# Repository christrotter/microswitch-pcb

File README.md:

# microswitch-pcb
Designed for use on the [ArcPedals mk2](https://github.com/christrotter/qmk_firmware/tree/arcboard-series/keyboards/handwired/arcpedals_mk2) - with the accompanying files, a drop-in replacement for the old MX-based switches.

JLC wanted to charge me extra for using SK6812-MINI-E leds, so I swapped over to the SK6805 and tripled the led count.  As one does.

# Overview
Only items of note - the pour is on the top layer only, and I tried to make it as friendly for manufacturing and human usage as possible.

## Parts
Gerbers, bom, position files and more in the releases section.

- 0402 100nF multilayer ceramic capacitor
- SOD-123F 1N4148W diode
- Omron D2F-L microswitch (key point, plunger only; heavier spring cuz feet)
- JST-XH-2.54 horizontal (or vertical, up to you) 6-pin connector
- 3x SK6805-EC15 LEDs

# Schematic overview
Pretty straightforward.
- 2.54 header (I designed for JST-XH 2.54 horizontal)
- 5v/GND power system w. 100nF capacitor
- LED signal via DI/DO pins
- 'key' signal via IN/OUT pins w. default diode on return leg
  - optionally cut the 2/3 bridge trace and solder pads 1/2 together for the direct pin (to GND)

# 3d view

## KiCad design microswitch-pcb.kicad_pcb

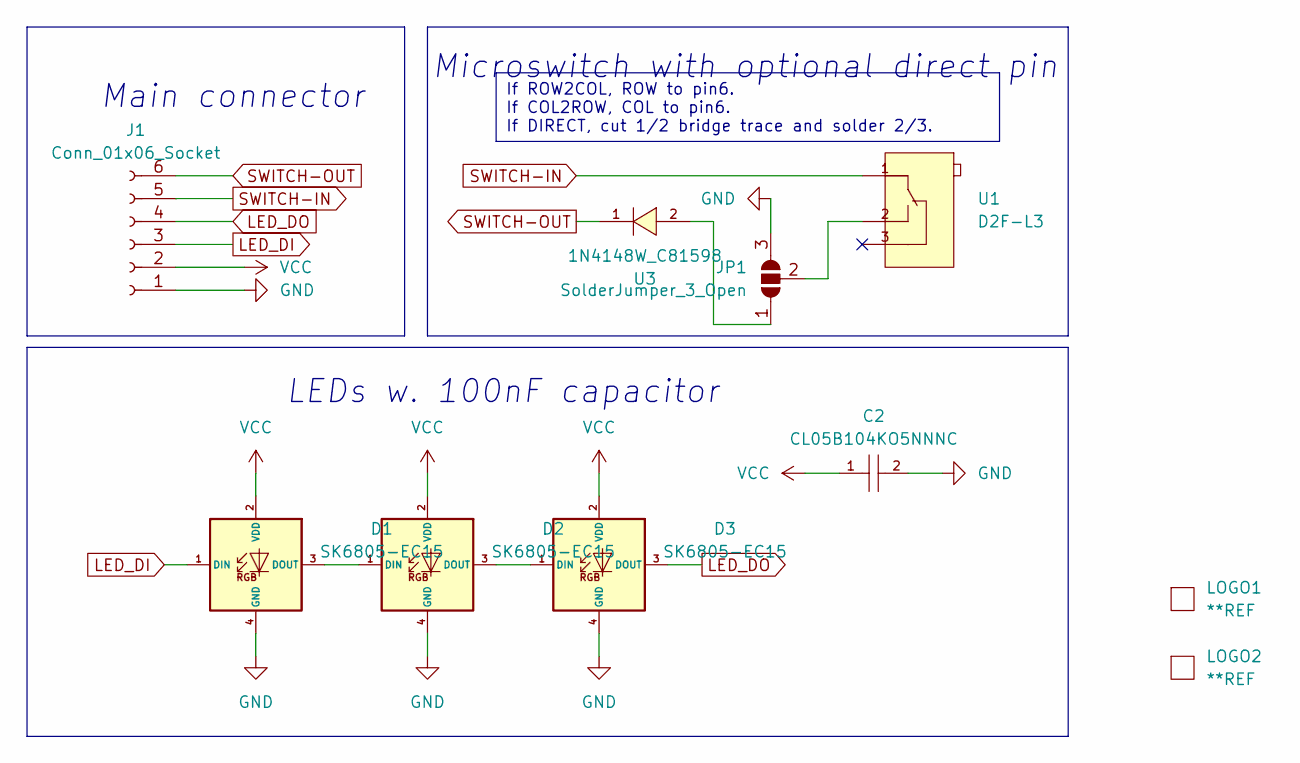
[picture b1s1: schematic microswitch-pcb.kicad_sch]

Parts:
C2: CL05B104KO5NNNC; C0402; LCSC C1525
D1, D2, D3: SK6805-EC15; LED_dilemma_SK6805-EC15_1.5x1.5mm_P0.6mm_handsolder; MPN SK6805-EC15; LCSC C2890035
J1: Conn_01x06_Socket; JST_XH_S6B-XH-A_1x06_P2.50mm_Horizontal
JP1: SolderJumper_3_Open; SolderJumper-3_P1.3mm_Bridged12_RoundedPad1.0x1.5mm_NumberL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
LOGO1, LOGO2: **REF; awesome-logo
U1: D2F-L3; SW-TH_D2F-L; LCSC C469124
U3: 1N4148W_C81598; SOD-123F_L2.7-W1.6-LS3.8-RD; LCSC C81598

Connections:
GND: C2.2, D1.4 (GND), D2.4 (GND), D3.4 (GND), J1.1, JP1.3 (B)
LED_DI: D1.1 (DIN), J1.3
LED_DO: D3.3 (DOUT), J1.4
unnamed: D1.3 (DOUT), D2.1 (DIN)
unnamed: D2.3 (DOUT), D3.1 (DIN)
unnamed: JP1.1 (A), U3.2 (A)
unnamed: JP1.2 (C), U1.2 (NO)
SWITCH-IN: J1.5, U1.1 (COM)
SWITCH-OUT: J1.6, U3.1 (K)
VCC: C2.1, D1.2 (VDD), D2.2 (VDD), D3.2 (VDD), J1.2

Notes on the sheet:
If ROW2COL, ROW to pin6. If COL2ROW, COL to pin6. If DIRECT, cut 1/2 bridge trace and solder 2/3.
Main connector
Microswitch with optional direct pin
LEDs w. 100nF capacitor

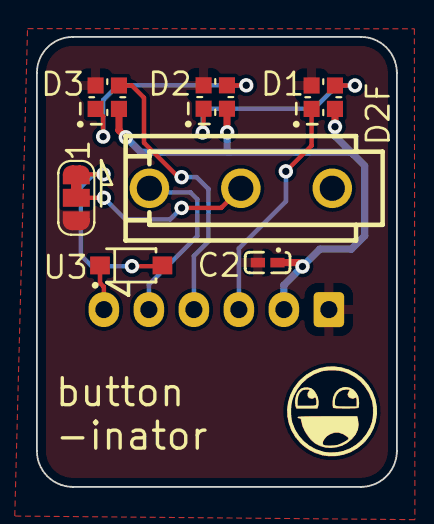
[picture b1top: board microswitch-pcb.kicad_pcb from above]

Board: 2 copper layers, 20.0 x 25.0 mm, 10 parts (1 on the bottom side), 10 nets.

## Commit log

2024-03-09 order placed
2024-03-09 adding readme
2024-03-09 inator
